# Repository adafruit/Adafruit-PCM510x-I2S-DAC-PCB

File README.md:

## Adafruit PCM510x I2S DAC with Line Level Output PCB

<a href="http://www.adafruit.com/products/6250"><br/>
Click here to purchase one from the Adafruit shop</a>
<br>
<a href="http://www.adafruit.com/products/6251"><br/>
Click here to purchase one from the Adafruit shop</a>

PCB files for the Adafruit PCM510x I2S DAC with Line Level Output. 

Format is EagleCAD schematic and board layout
* https://www.adafruit.com/product/6250
* https://www.adafruit.com/product/6251

### Description

We stock a lot of chips and development boards that are able to do high quality digital I2S out, which makes for great quality audio playback. That's great when you have enough processing power to decode WAVs or MP3s in real time. However, we don't have a good selection of I2S DAC boards...until now! We really love the sounds coming out of the Adafruit PCM5102 I2S DAC with Line Level Output - it's got clean, excellent-quality, stereo audio and does not need any MCLK or I2C configuration. Literally just pipe some I2S audio in and it ill just work.

The PCM510x comes in a few different varieties: we've got the the good-quality PCM5100 with 100dB signa-to-noise/dynamic range, and the excellent-quality PCM5102 with 112dB. The '02 is a little more expensive but they are both quite good for any use and are pin-compatible so can swap between the two.

This breakout makes I2S digital audio easy: all you need to do is power it with 3~5VDC, and provide BCLK (bit clock), WSEL (left/right word select), and DIN (data in). The data lines are 3.3V logic only. By default it's configured for I2S but you can also do Left-Justified by toggling the Format pin. Audio can be 16, 24 or 32-bit wide, the chip will automagically determine the right format from the WSEL / BCLK ratio. No MCLK pin is needed, the chip will auto-generate it internally from the bit clock - or you can provide it on the MCLK input if you want.

Other breakout pads provide: filtering (change from normal to low-latency by pulling high), mute (pull low to quickly set the outputs to ground), and de-emphasis for 44.1khz audio (default is off). The audio outputs are also available on breakout pads if you want to wire directly without using the 3.5mm jack.

Audio output is not AC-coupled because it is centered on ground: you can plug it into anything that is either AC coupled or has the same ground reference. Note that this is a line-level output, it cannot drive headphones - the output is for no less than 1K ohm loads!

Each order comes with one I2S Stereo DAC breakout and some header you can solder on for breadboard usage.

### License

Adafruit invests time and resources providing this open source design, please support Adafruit and open-source hardware by purchasing products from [Adafruit](https://www.adafruit.com)!

Designed by Limor Fried/Ladyada for Adafruit Industries.

Creative Commons Attribution/Share-Alike, all text above must be included in any redistribution. 
See license.txt for additional details.

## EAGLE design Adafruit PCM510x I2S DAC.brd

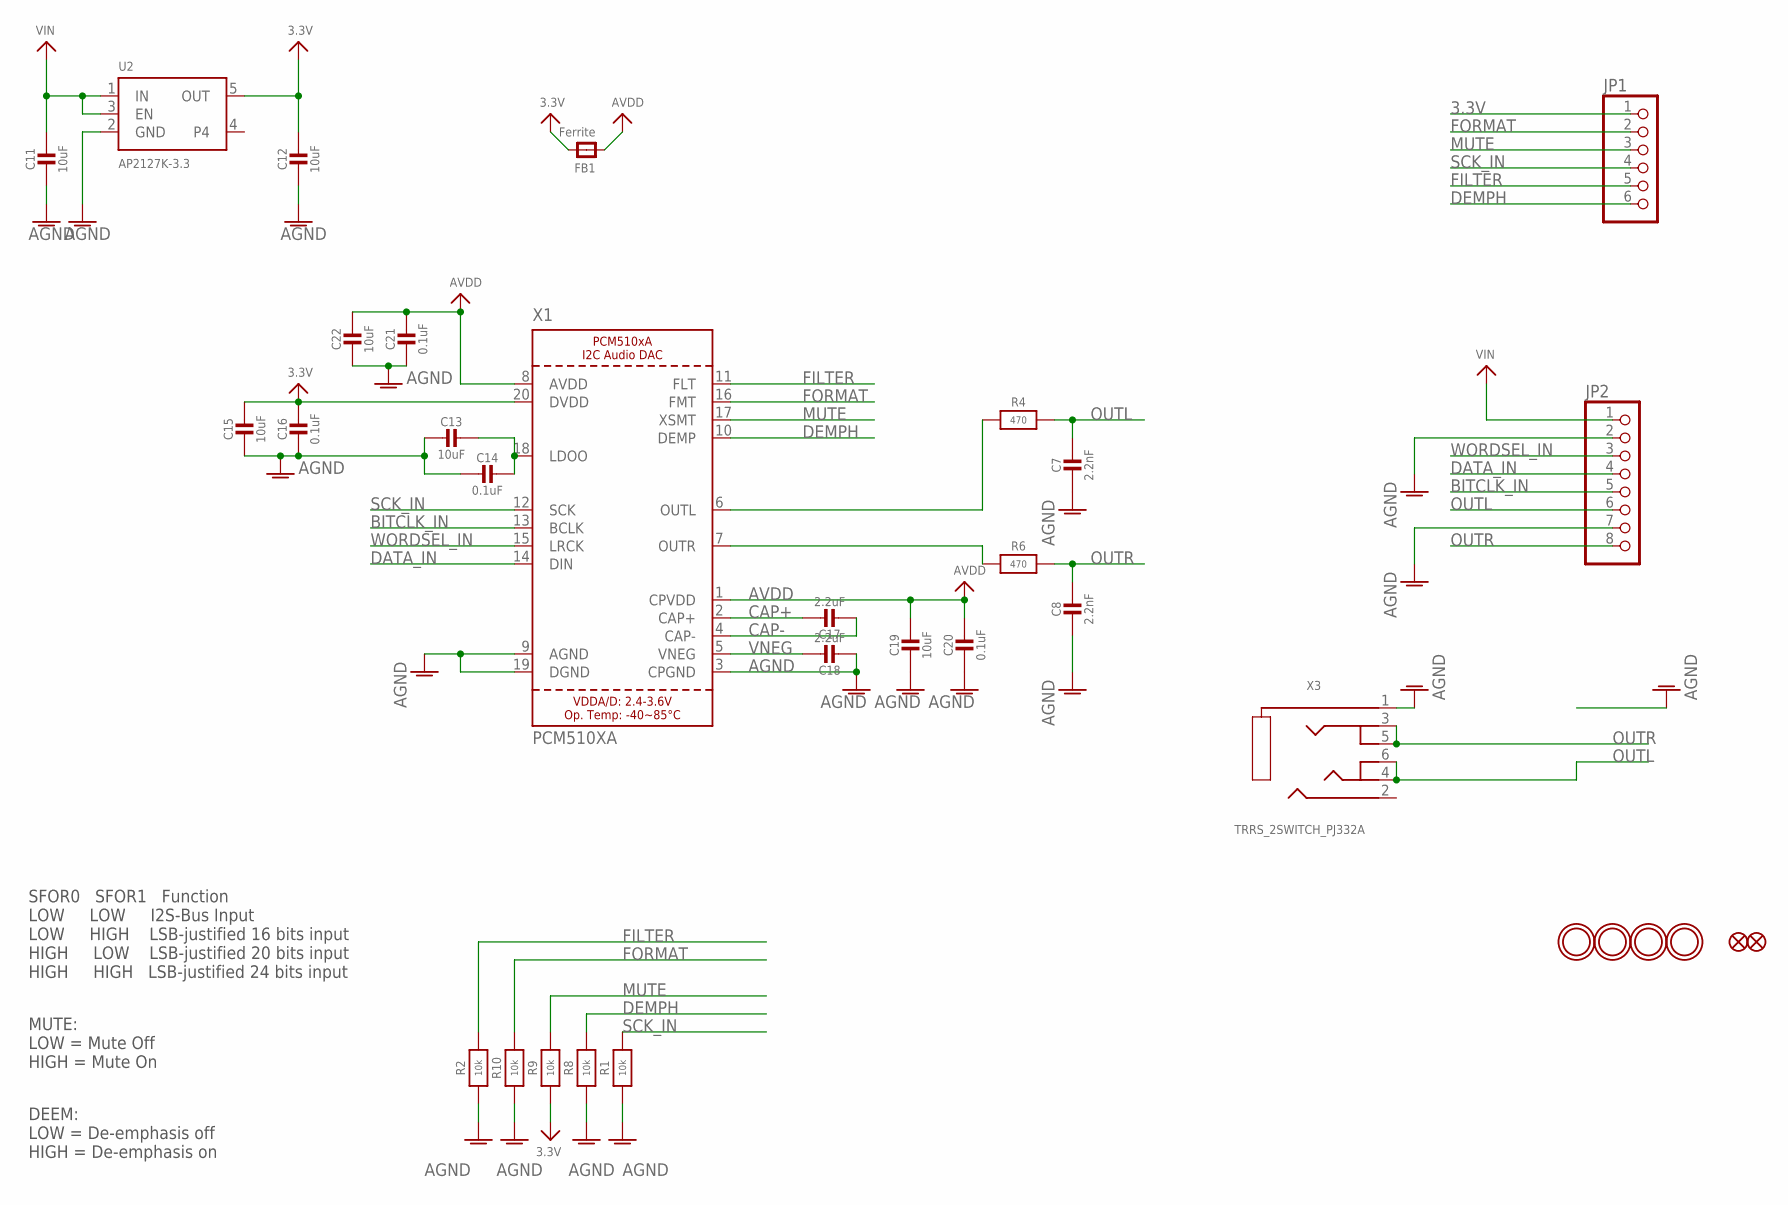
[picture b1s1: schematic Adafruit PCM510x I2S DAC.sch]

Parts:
C7, C8: 2.2nF; 0603-NO
C11, C12, C13, C15, C19, C22: 10uF; 0805-NO
C14, C16, C20, C21: 0.1uF; 0603-NO
C17, C18: 2.2uF; 0603-NO
FB1: Ferrite; 0603-NO
FID1, FID2: FIDUCIAL_0.5MM
JP1: HEADER-1X670MIL; 1X06_ROUND_70
JP2: HEADER-1X8ROUND; 1X08_ROUND
R1, R2, R8, R9, R10: 10k; 0603-NO
R4, R6: 470; 0603-NO
U2: AP2127K-3.3; SOT23-5
U$11, U$12, U$13, U$14: MOUNTINGHOLE2.5; MOUNTINGHOLE_2.5_PLATED
X1: PCM510XA; TSSOP20
X3: TRRS_2SWITCH_PJ332A; PJ-332A

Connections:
3.3V: C12.1, C15.1, C16.1, FB1.2, JP1.1, R9.1, U2.5 (OUT), X1.20 (DVDD)
AGND: C7.2, C8.2, C11.2, C12.2, C13.2, C14.2, C15.2, C16.2, C18.2, C19.2, C20.2, C21.2, C22.2, JP2.2, JP2.7, R1.1, R2.1, R8.1, R10.1, U2.2 (GND), X1.3 (CPGND), X1.9 (AGND), X1.19 (DGND), X3.1 (RING)
AVDD: C19.1, C20.1, C21.1, C22.1, FB1.1, X1.1 (CPVDD), X1.8 (AVDD)
BITCLK_IN: JP2.5, X1.13 (BCLK)
CAP+: C17.1, X1.2 (CAP+)
CAP-: C17.2, X1.4 (CAP-)
DATA_IN: JP2.4, X1.14 (DIN)
DEMPH: JP1.6, R8.2, X1.10 (DEMP)
FILTER: JP1.5, R2.2, X1.11 (FLT)
FORMAT: JP1.2, R10.2, X1.16 (FMT)
MUTE: JP1.3, R9.2, X1.17 (XSMT)
unnamed: R6.1, X1.7 (OUTR)
unnamed: R4.1, X1.6 (OUTL)
unnamed: C13.1, C14.1, X1.18 (LDOO)
OUTL: C7.1, JP2.6, R4.2, X3.4 (TIP), X3.6 (TIP_SW)
OUTR: C8.1, JP2.8, R6.2, X3.3 (RING2), X3.5 (R2_SW)
SCK_IN: JP1.4, R1.2, X1.12 (SCK)
VIN: C11.1, JP2.1, U2.1 (IN), U2.3 (EN)
VNEG: C18.1, X1.5 (VNEG)
WORDSEL_IN: JP2.3, X1.15 (LRCK)

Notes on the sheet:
MUTE: LOW = Mute Off HIGH = Mute On
DEEM: LOW = De-emphasis off HIGH = De-emphasis on
SFOR0 SFOR1 Function LOW LOW I2S-Bus Input LOW HIGH LSB-justified 16 bits input HIGH LOW LSB-justified 20 bits input HIGH HIGH LSB-justified 24 bits input

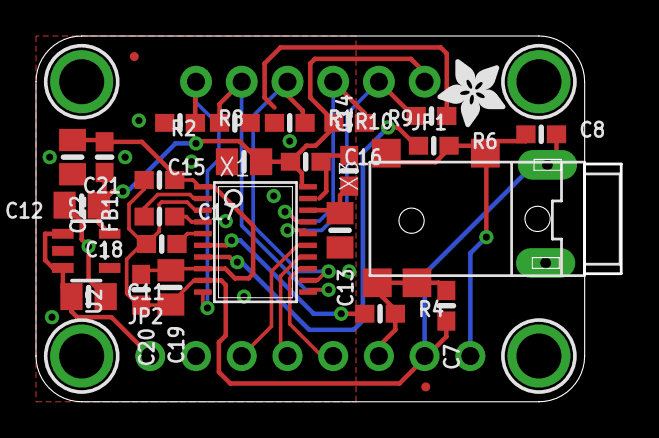
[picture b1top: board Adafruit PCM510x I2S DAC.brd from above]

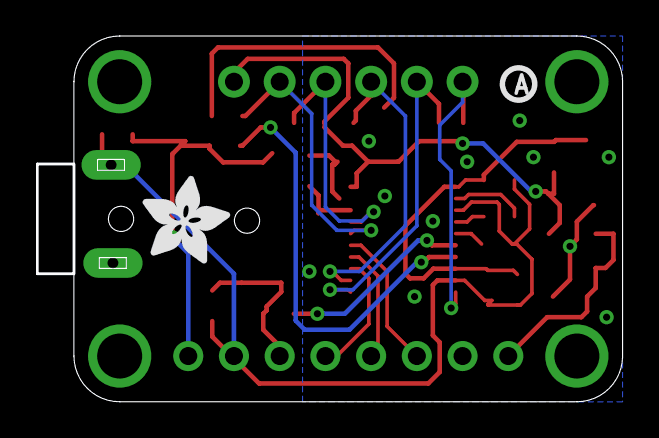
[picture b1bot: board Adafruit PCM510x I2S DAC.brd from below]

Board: 2 copper layers, 32.4 x 20.2 mm, 54 parts (5 on the bottom side), 20 nets.

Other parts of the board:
PLABEL0: PLABEL0
PLABEL1: PLABEL1
PLABEL2: PLABEL2
PLABEL3: PLABEL3
PLABEL4: PLABEL4
PLABEL5: PLABEL5
PLABEL6: PLABEL6
PLABEL7: PLABEL7
PLABEL8: PLABEL8
PLABEL9: PLABEL9
PLABEL10: PLABEL10
PLABEL11: PLABEL11
PLABEL12: PLABEL12
PLABEL13: PLABEL13
PLABEL16: PLABEL16
PLABEL17: PLABEL17
PLABEL18: PLABEL18
PLABEL19: PLABEL19
U$5: PCBFEAT-REV-040
U$6: ADAFRUIT_5MM
U$29: ADAFRUIT_3.5MM

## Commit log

2025-03-03 cookiecutter

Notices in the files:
parts and their libraries:
microbuilder: This work is placed in the public domain, and may be freely used for commercial and non-commercial work with the following conditions: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
